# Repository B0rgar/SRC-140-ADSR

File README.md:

# SRC-140-ADSR
 Dual ADSR based on Eagleproject from Gerbster.nl.

imported to kicad. panel made. I regret not changing to thonkicon jacks.
PCBS ordered from JLCPCB. will update after building and testing.

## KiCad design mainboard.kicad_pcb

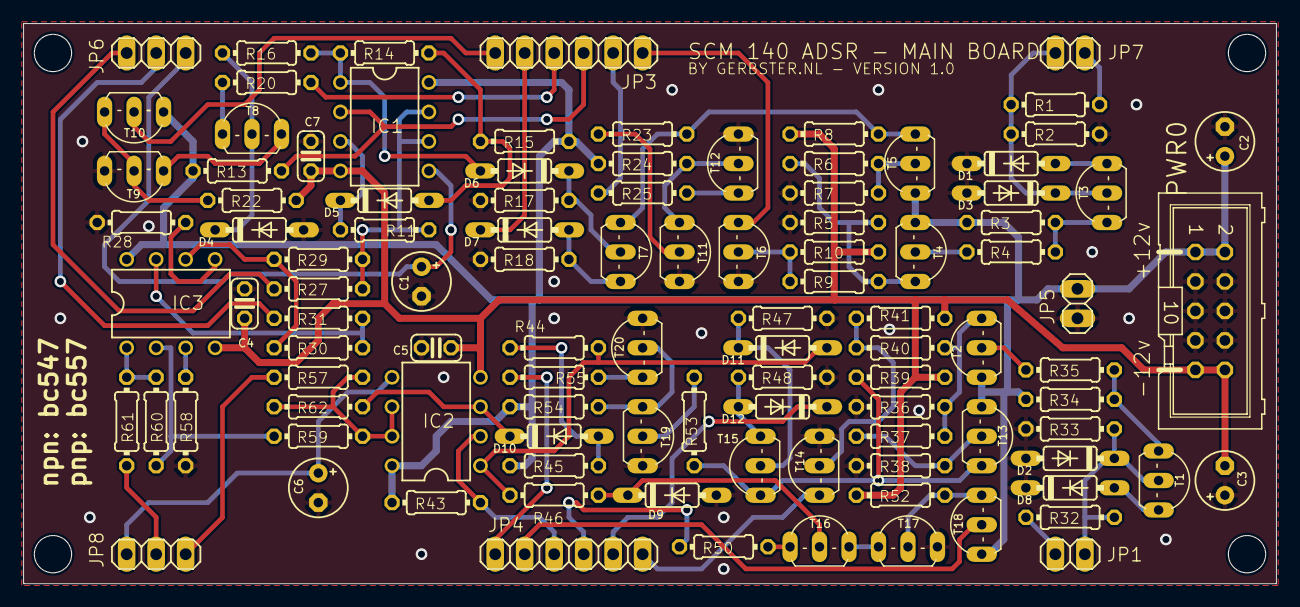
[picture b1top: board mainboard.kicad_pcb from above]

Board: 2 copper layers, 108.0 x 48.3 mm, 108 parts (0 on the bottom side), 71 nets.

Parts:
@HOLE0, @HOLE1, @HOLE2, @HOLE3: (no value)
C1, C6: 3.3u/35v; E2,5-5
C2, C3: 47u/16v; E2,5-5
C4, C5, C7: 0.01u; C025-024X044
D1, D2, D3, D4, D5, D6, D7, D8, D9, D10, D11, D12: DO35-7
IC1, IC2, IC3: LM4558N; DIL08
JP1, JP5, JP7: 1X02
JP3, JP4: 1X06
JP6, JP8: 1X03
PWR0: ML10
R1, R18, R32, R48: 33k; 0204_7
R2, R4, R6, R15, R33, R35, R37, R45: 22k; 0204_7
R3, R5, R24, R34, R36, R54: 10k; 0204_7
R7, R38: 150k; 0204_7
R8, R11, R13, R17, R28, R39, R43, R47, R58, R62: 47k; 0204_7
R9, R14, R40, R44: 56k; 0204_7
R10, R41: 560k; 0204_7
R16, R23, R29, R30, R46, R53, R59, R60: 100k; 0204_7
R20, R25, R50, R55: 330; 0204_7
R22, R52: 15k; 0204_7
R27, R31, R57, R61: 1k; 0204_7
T1, T3, T5, T6, T8, T10, T11, T12, T13, T14, T16, T18, T19, T20: BC547; TO92-CBE
T2, T4, T7, T9, T15, T17: BC557B; TO92-EBC

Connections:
+12V: C2.+, IC1.8, IC2.8, IC3.8, JP5.2, PWR0.1, PWR0.2, R3.2, R13.2, R15.2, R24.2, R34.2, R43.2, R45.2, R54.2, T2.E, T4.E, T5.C, T10.C, T13.C, T18.C
-12V: C3.-, C4.1, C5.1, C7.1, IC1.4, IC2.4, IC3.4, PWR0.9, PWR0.10, R8.1, R10.1, R22.1, R39.1, R41.1, R52.1
A1-IN: D7.C, JP3.5
A2-IN: D12.C, JP4.5
C1-OUT: C1.+, IC1.5, JP6.1
C2-OUT: C6.+, IC2.5, JP8.1
D1-IN: JP3.4, R20.2
D2-IN: JP4.4, R50.2
GATE-1: JP7.2, R1.1
GATE-2: JP1.2, R32.1
GND: C1.-, C2.-, C3.+, C4.2, C5.2, C6.-, C7.2, D1.A, D2.A, D3.C, D4.A, D8.C, D9.A, JP5.1, PWR0.3, PWR0.4, PWR0.5, PWR0.6, PWR0.7, PWR0.8, R2.1, R5.1, R7.1, R17.1, R18.1, R28.1, R33.1, R36.1, R38.1, R47.1, R48.1, R58.1, T6.E, T9.C, T11.E, T12.E, T14.E, T17.C, T19.E, T20.E
INV-OUT-1: JP6.2, R31.2
INV-OUT-2: JP8.2, R61.2
MANUAL-TRIGGER-1: D1.C, JP7.1, R1.2, R2.2, T3.B
MANUAL-TRIGGER-2: D2.C, JP1.1, R32.2, R33.2, T1.B
unnamed: D5.C, IC1.3, R11.1
unnamed: D3.A, T3.E
unnamed: R3.1, R4.1, T3.C
unnamed: R4.2, T4.B
unnamed: R5.2, R6.1, R9.2, T4.C
unnamed: R8.2, R23.1, T5.E, T7.E
unnamed: R6.2, R7.2, T5.B
unnamed: R9.1, R10.2, T6.B
unnamed: D6.A, IC1.1, R14.1, R16.2
unnamed: D4.C, R16.1, T8.B
unnamed: D5.A, R14.2, R15.1
unnamed: IC1.6, IC1.7, R11.2, R27.1, R29.2
unnamed: D7.A, R18.2, T7.C
unnamed: D6.C, R17.2, T7.B
unnamed: IC3.6, R29.1, R30.1
unnamed: R20.1, T8.C
unnamed: R22.2, T9.B, T10.E
unnamed: T8.E, T9.E
unnamed: R23.2, T11.B
unnamed: R24.1, T11.C, T12.B
unnamed: R25.1, T12.C
unnamed: IC3.7, R30.2, R31.1
unnamed: D8.A, T1.E
unnamed: IC3.5, R28.2
unnamed: R34.1, R35.1, T1.C
unnamed: R35.2, T2.B
unnamed: R36.2, R37.1, R40.2, T2.C
unnamed: R39.2, R53.1, T13.E, T15.E
unnamed: R37.2, R38.2, T13.B
unnamed: R40.1, R41.2, T14.B
unnamed: D11.A, IC2.1, R44.1, R46.2
unnamed: D9.C, R46.1, T16.B
unnamed: D10.A, R44.2, R45.1
unnamed: IC2.6, IC2.7, R57.1, R59.2, R62.2
unnamed: D11.C, R47.2, T15.B
unnamed: D12.A, R48.2, T15.C
unnamed: R50.1, T16.C
unnamed: R52.2, T17.B, T18.E
unnamed: T16.E, T17.E
unnamed: R53.2, T19.B
unnamed: R54.1, T19.C, T20.B
unnamed: R55.1, T20.C
unnamed: IC3.2, R59.1, R60.1
unnamed: IC3.1, R60.2, R61.1
unnamed: IC3.3, R58.2
unnamed: D10.C, IC2.3, R62.1
NORM-OUT-1: JP6.3, R27.2
NORM-OUT-2: JP8.3, R57.2
R1-IN: JP3.2, R25.2
R2-IN: JP4.1, R55.2
S1-A: IC1.2, JP3.3, R13.1
S1-B: JP3.1, T6.C
S1-W: JP3.6, T10.B
S2-A: IC2.2, JP4.3, R43.1
S2-B: JP4.6, T14.C
S2-W: JP4.2, T18.B

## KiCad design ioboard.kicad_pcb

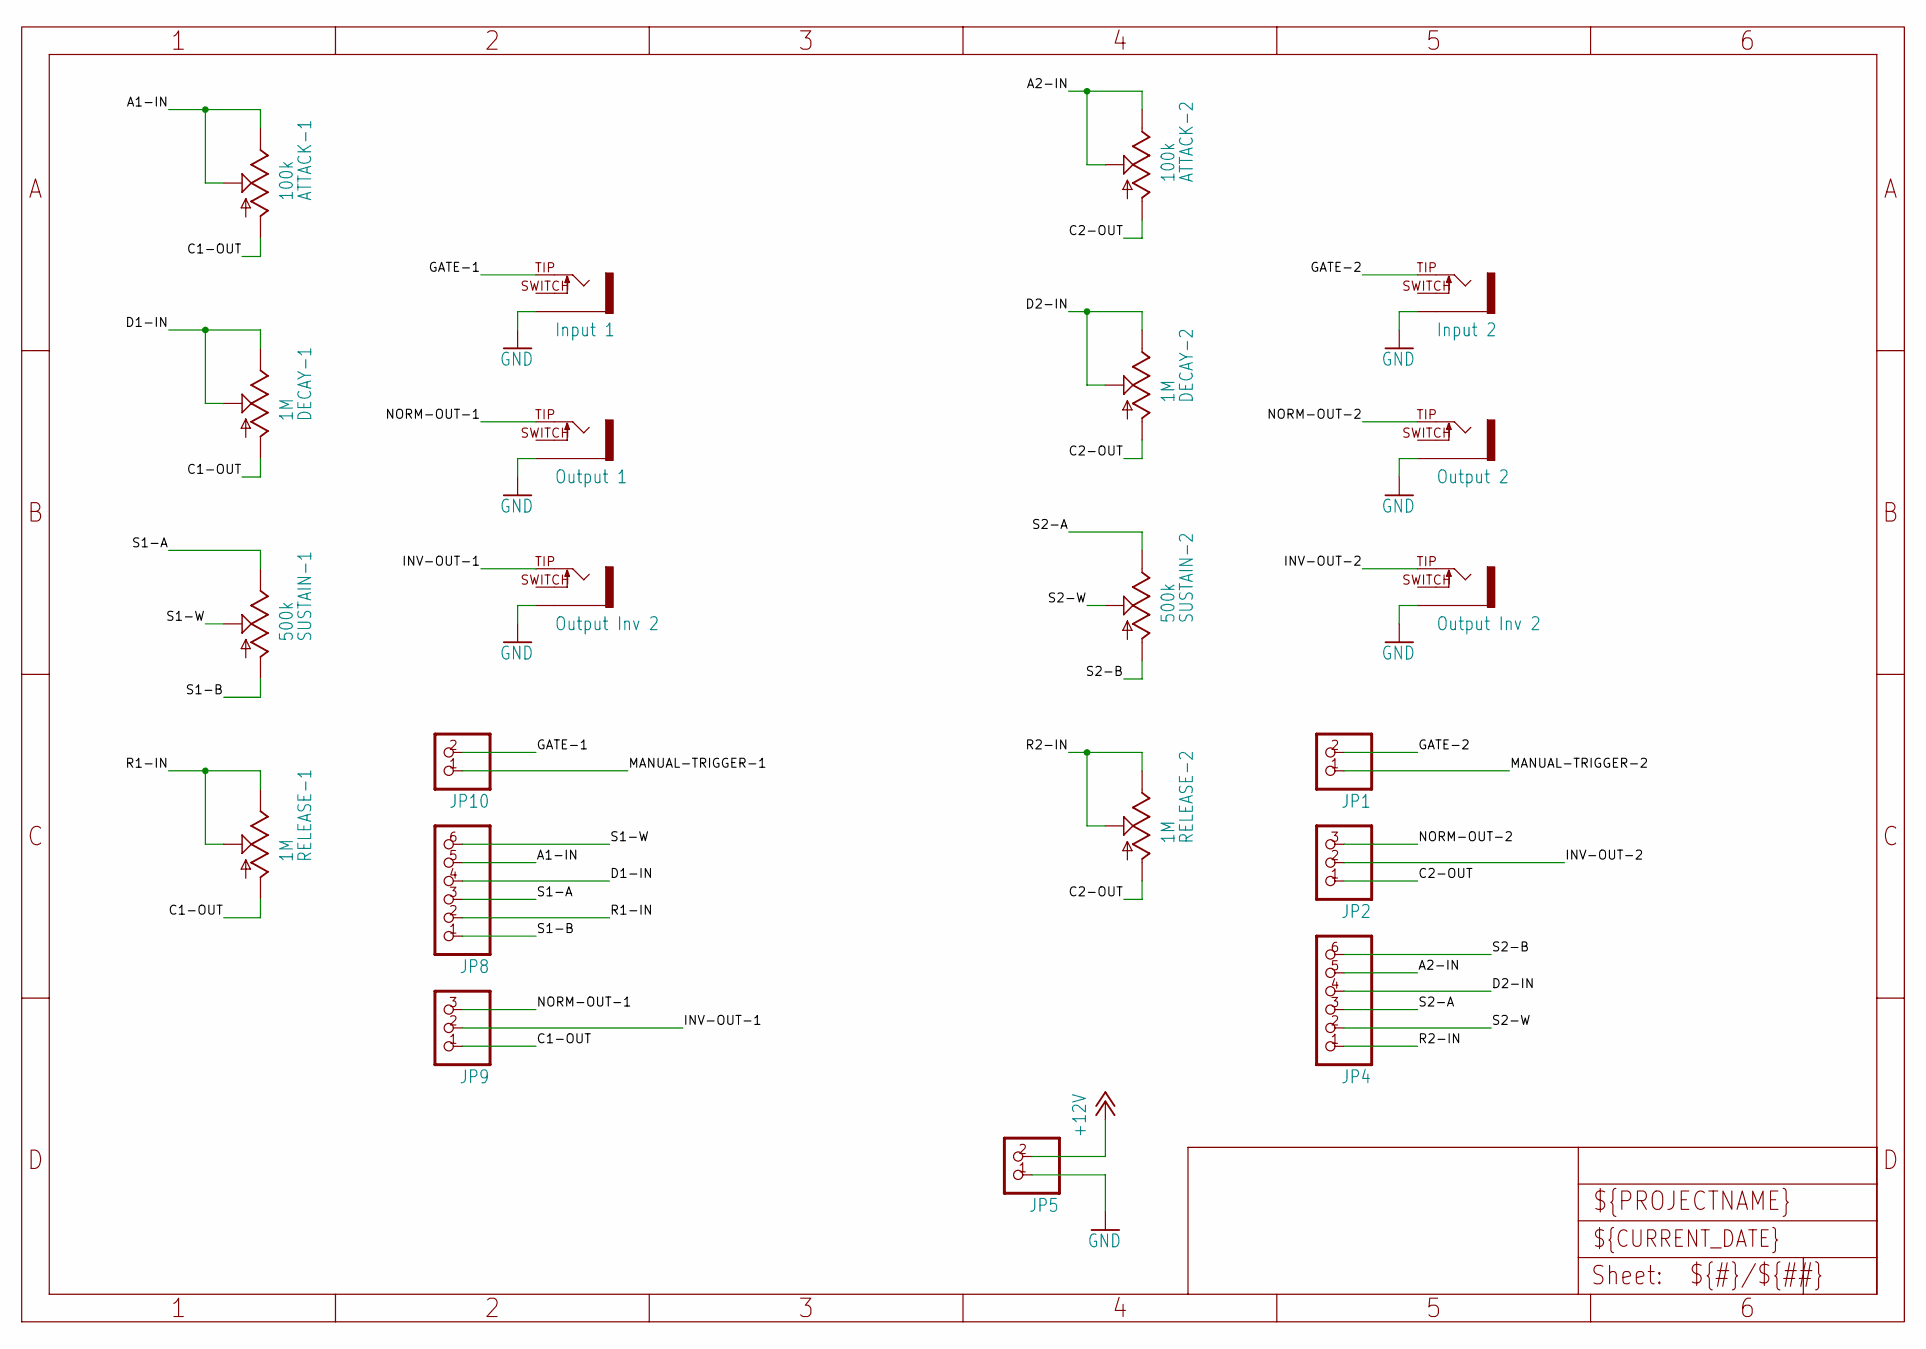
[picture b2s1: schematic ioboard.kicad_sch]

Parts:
ATTACK-1, ATTACK-2: 100k; EVUF
DECAY-1, DECAY-2: 1M; EVUF
GATE1: Input 1; PJ301BM
GATE2: Input 2; PJ301BM
INV-OUT1, INV-OUT2: Output Inv 2; PJ301BM
JP1, JP5, JP10: PINHD-1X2; 1X02
JP2, JP9: PINHD-1X3; 1X03
JP4, JP8: PINHD-1X6; 1X06
NORM-OUT1: Output 1; PJ301BM
NORM-OUT2: Output 2; PJ301BM
RELEASE-1, RELEASE-2: 1M; EVUF
SUSTAIN-1, SUSTAIN-2: 500k; EVUF

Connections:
+12V: JP5.2
A1-IN: ATTACK-1.2 (S), ATTACK-1.3 (E), JP8.5
A2-IN: ATTACK-2.2 (S), ATTACK-2.3 (E), JP4.5
C1-OUT: ATTACK-1.1 (A), DECAY-1.1 (A), JP9.1, RELEASE-1.1 (A)
C2-OUT: ATTACK-2.1 (A), DECAY-2.1 (A), JP2.1, RELEASE-2.1 (A)
D1-IN: DECAY-1.2 (S), DECAY-1.3 (E), JP8.4
D2-IN: DECAY-2.2 (S), DECAY-2.3 (E), JP4.4
GATE-1: GATE1.TIP (3), JP10.2
GATE-2: GATE2.TIP (3), JP1.2
GND: GATE1.GND1 (5), GATE1.GND2 (5), GATE2.GND1 (5), GATE2.GND2 (5), INV-OUT1.GND1 (5), INV-OUT1.GND2 (5), INV-OUT2.GND1 (5), INV-OUT2.GND2 (5), JP5.1, NORM-OUT1.GND1 (5), NORM-OUT1.GND2 (5), NORM-OUT2.GND1 (5), NORM-OUT2.GND2 (5)
INV-OUT-1: INV-OUT1.TIP (3), JP9.2
INV-OUT-2: INV-OUT2.TIP (3), JP2.2
MANUAL-TRIGGER-1: JP10.1
MANUAL-TRIGGER-2: JP1.1
NORM-OUT-1: JP9.3, NORM-OUT1.TIP (3)
NORM-OUT-2: JP2.3, NORM-OUT2.TIP (3)
R1-IN: JP8.2, RELEASE-1.2 (S), RELEASE-1.3 (E)
R2-IN: JP4.1, RELEASE-2.2 (S), RELEASE-2.3 (E)
S1-A: JP8.3, SUSTAIN-1.3 (E)
S1-B: JP8.1, SUSTAIN-1.1 (A)
S1-W: JP8.6, SUSTAIN-1.2 (S)
S2-A: JP4.3, SUSTAIN-2.3 (E)
S2-B: JP4.6, SUSTAIN-2.1 (A)
S2-W: JP4.2, SUSTAIN-2.2 (S)

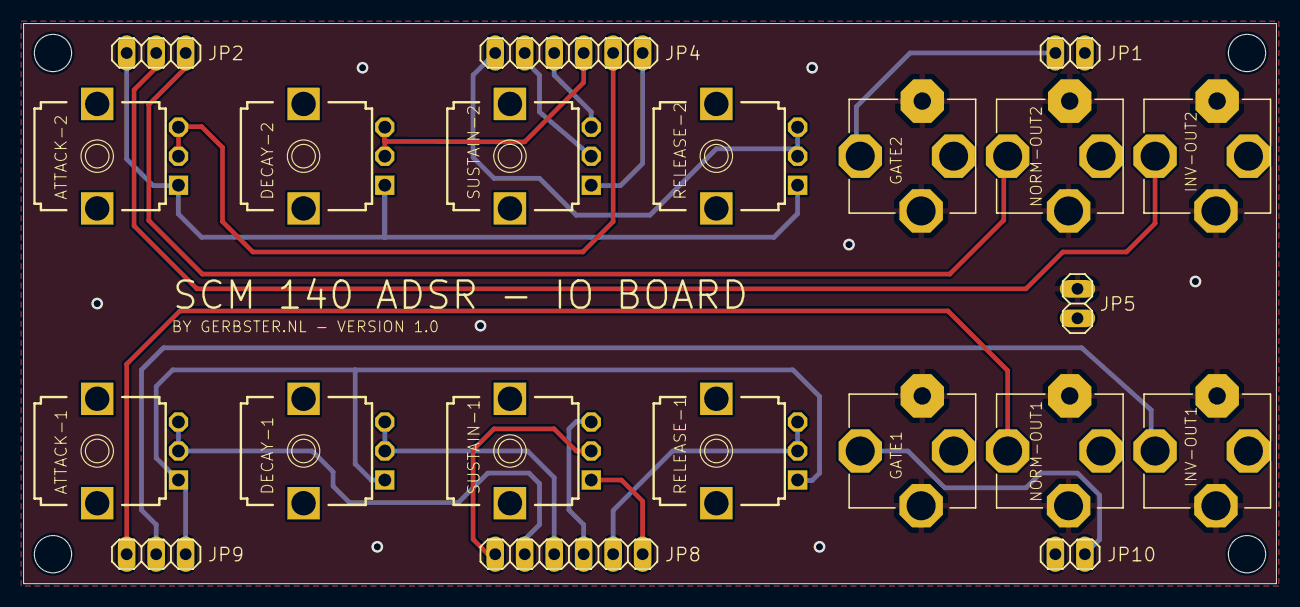
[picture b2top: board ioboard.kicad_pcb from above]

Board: 2 copper layers, 108.0 x 48.3 mm, 25 parts (0 on the bottom side), 21 nets.

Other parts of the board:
@HOLE0, @HOLE1, @HOLE2, @HOLE3: (no value)

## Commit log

2025-03-03 prod files and ibom
2025-03-03 panel3d pic test
2025-03-16 pisc
